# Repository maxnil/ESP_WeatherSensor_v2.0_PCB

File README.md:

# ESP_WeatherStation_v2.0_PCB
Simple weather station v2.0 (temperature, humidity and air pressure) based around a ESP8266 module

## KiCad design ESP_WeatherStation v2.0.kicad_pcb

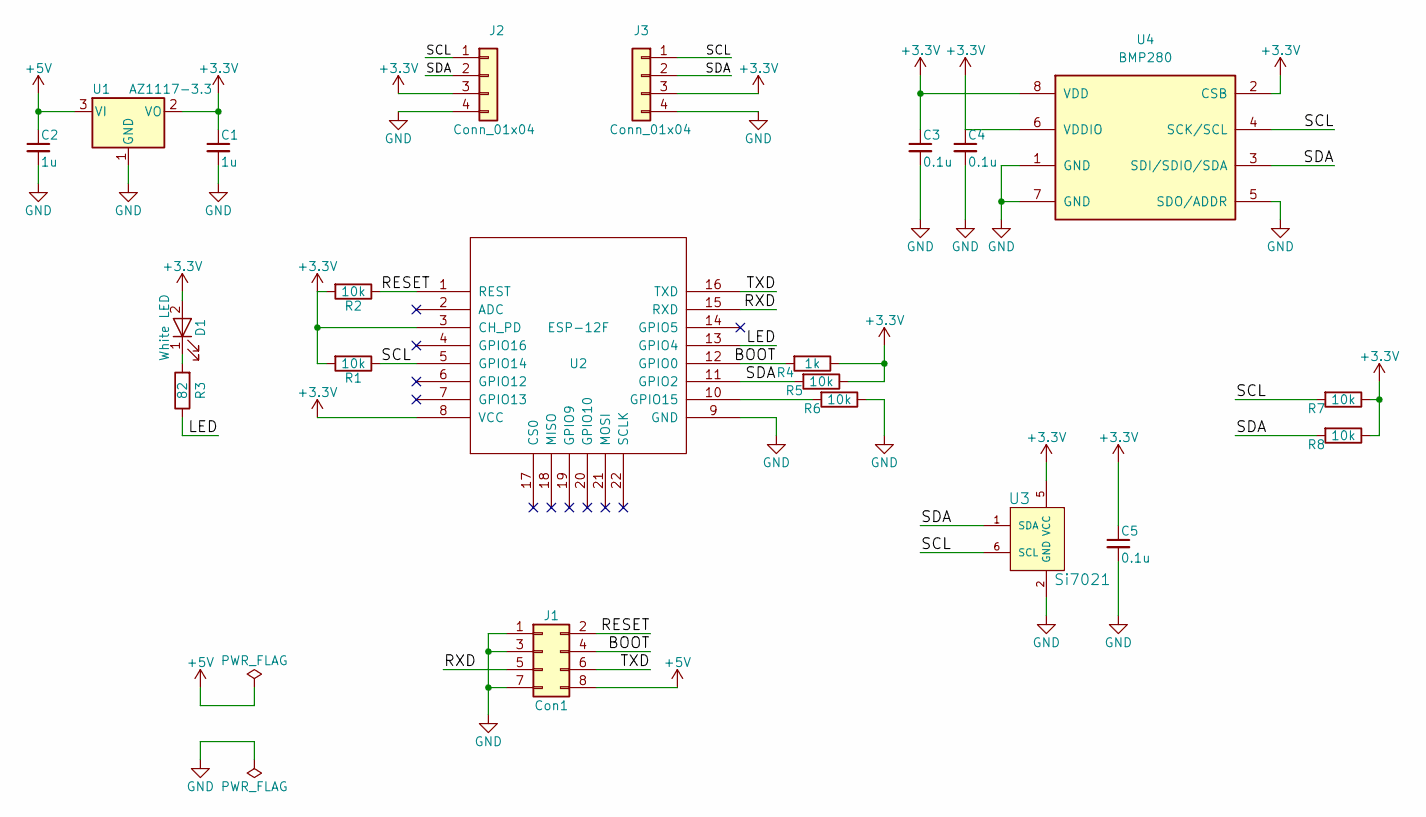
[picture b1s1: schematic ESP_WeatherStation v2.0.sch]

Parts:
C1, C2: 1u; C_0603
C3, C4, C5: 0.1u; C_0603
D1: White LED; LED_0603
J1: Con1; Pin_Header_Straight_2x04_Pitch2.54mm_SMD
J2, J3: Conn_01x04; Pin_Header_Straight_1x04_Pitch1.27mm
R1, R2, R5, R6, R7, R8: 10k; R_0603
R3: 82; R_0603
R4: 1k; R_0603
U1: AZ1117-3.3; SOT-223
U2: ESP-12F; ESP-12E_SMD
U3: Si7021; DFN-6-1EP_3x3mm_Pitch0.95mm
U4: BMP280; BOSCH_BMP280; MPN BMP280

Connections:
+3V3: C1.1, C3.1, C4.1, C5.1, D1.2 (A), J2.3, J3.3, R1.2, R2.2, R4.1, R5.1, R7.1, R8.1, U1.2 (VO), U2.3 (CH_PD), U2.8 (VCC), U3.5 (VCC), U4.2 (CSB), U4.6 (VDDIO), U4.8 (VDD)
+5V: C2.1, J1.8, U1.3 (VI)
/BOOT: J1.4, R4.2, U2.12 (GPIO0)
/LED: R3.1, U2.13 (GPIO4)
/RESET: J1.2, R2.1, U2.1 (REST)
/RXD: J1.5, U2.15 (RXD)
/SCL: J2.1, J3.1, R1.1, R7.2, U2.5 (GPIO14), U3.6 (SCL), U4.4 (SCK/SCL)
/SDA: J2.2, J3.2, R5.2, R8.2, U2.11 (GPIO2), U3.1 (SDA), U4.3 (SDI/SDIO/SDA)
/TXD: J1.6, U2.16 (TXD)
GND: C1.2, C2.2, C3.2, C4.2, C5.2, J1.1, J1.3, J1.7, J2.4, J3.4, R6.1, U1.1 (GND), U2.9 (GND), U3.2 (GND), U4.1 (GND), U4.5 (SDO/ADDR), U4.7 (GND)
unnamed: D1.1 (K), R3.2
unnamed: R6.2, U2.10 (GPIO15)

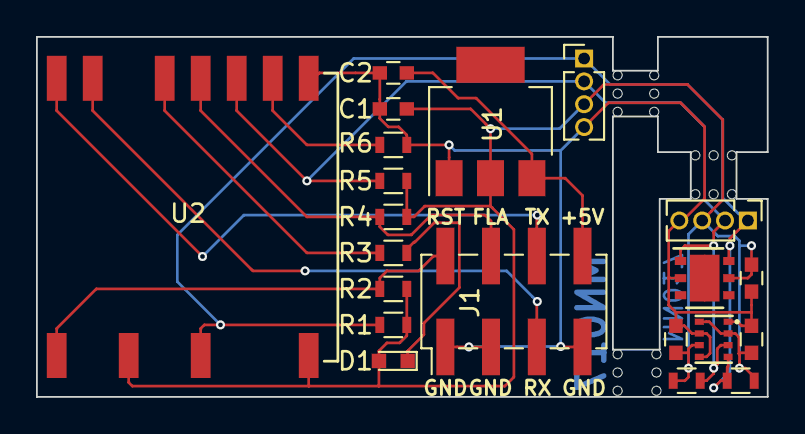
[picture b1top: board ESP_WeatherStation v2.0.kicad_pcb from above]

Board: 2 copper layers, 40.6 x 20.0 mm, 21 parts (0 on the bottom side), 12 nets.

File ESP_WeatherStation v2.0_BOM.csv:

Reference, Value, Footprint, Datasheet, BOM, MPN, Manuf
"U3","Si7021","Housings_DFN_QFN:DFN-6-1EP_3x3mm_Pitch0.95mm",""
"C5","0.1u","Capacitors_SMD:C_0603",""
"C3","0.1u","Capacitors_SMD:C_0603",""
"D1","White LED","LEDs:LED_0603",""
"R2","10k","Resistors_SMD:R_0603",""
"R1","10k","Resistors_SMD:R_0603",""
"R4","1k","Resistors_SMD:R_0603",""
"J1","Con1","Pin_Headers:Pin_Header_Straight_2x04_Pitch2.54mm_SMD",""
"U1","AZ1117-3.3","TO_SOT_Packages_SMD:SOT-223",""
"U4","BMP280","MaxNil:BOSCH_BMP280","https://ae-bst.resource.bosch.com/media/_tech/media/datashee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","Bosch BMP280","BMP280","Bosch"
"R5","10k","Resistors_SMD:R_0603",""
"R6","10k","Resistors_SMD:R_0603",""
"R3","82","Resistors_SMD:R_0603",""
"U2","ESP-12F","ESP8266:ESP-12E_SMD",""
"C4","0.1u","Capacitors_SMD:C_0603",""
"C1","1u","Capacitors_SMD:C_0603",""
"C2","1u","Capacitors_SMD:C_0603",""
"J2","Conn_01x04","Pin_Headers:Pin_Header_Straight_1x04_Pitch1.27mm","~"
"J3","Conn_01x04","Pin_Headers:Pin_Header_Straight_1x04_Pitch1.27mm","~"
"R7","10k","Resistors_SMD:R_0603",""
"R8","10k","Resistors_SMD:R_0603",""

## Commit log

2019-01-14 Released version (PCB made)
2019-05-15 Hepp
2019-05-15 Testing

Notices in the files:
ESP_WeatherStation v2.0.kicad_pcb:
(c)2018
(c)2018 MaxNil
